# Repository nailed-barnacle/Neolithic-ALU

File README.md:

# Neolithic-ALU
This is a simple 8-bit ALU based on Ken Shirriff's dissection of the 8085's ALU at https://www.righto.com/2013/01/inside-alu-of-8085-microprocessor.html

It takes two inputs - A and B - and a number of control inputs to provide an output, one of:
- A (bypass)
- A OR B
- A AND B
- A XOR B
- A plus B with carry
- A minus B with carry 
- Complement of B
- A shifted right

Notes:

The carry input and output for arithmetic operations is inverted. To add or subtract without carry, it must be set. For other logic operations it must be set or cleared.

The zero output is inverted (i.e. set if the output is not zero).

The sign output is simply bit 7 of the result.

The bit shifted out after a right shift is the lowest input bit; it has no dedicated output. A dedicated input - shift_in - provides the high bit of the shift result.

At the time of posting, the only parts available for all components were 74HC; the circuit will operate across the 74HC range but will be faster at 5v than 3v3. I still need to measure the propagation delay but expect it to be around 60-70ns at five volts. Other equivalant parts - e.g. AHC or VLC - will probably be faster. The critical path is the chain of OR gates running right to left through the circuit.

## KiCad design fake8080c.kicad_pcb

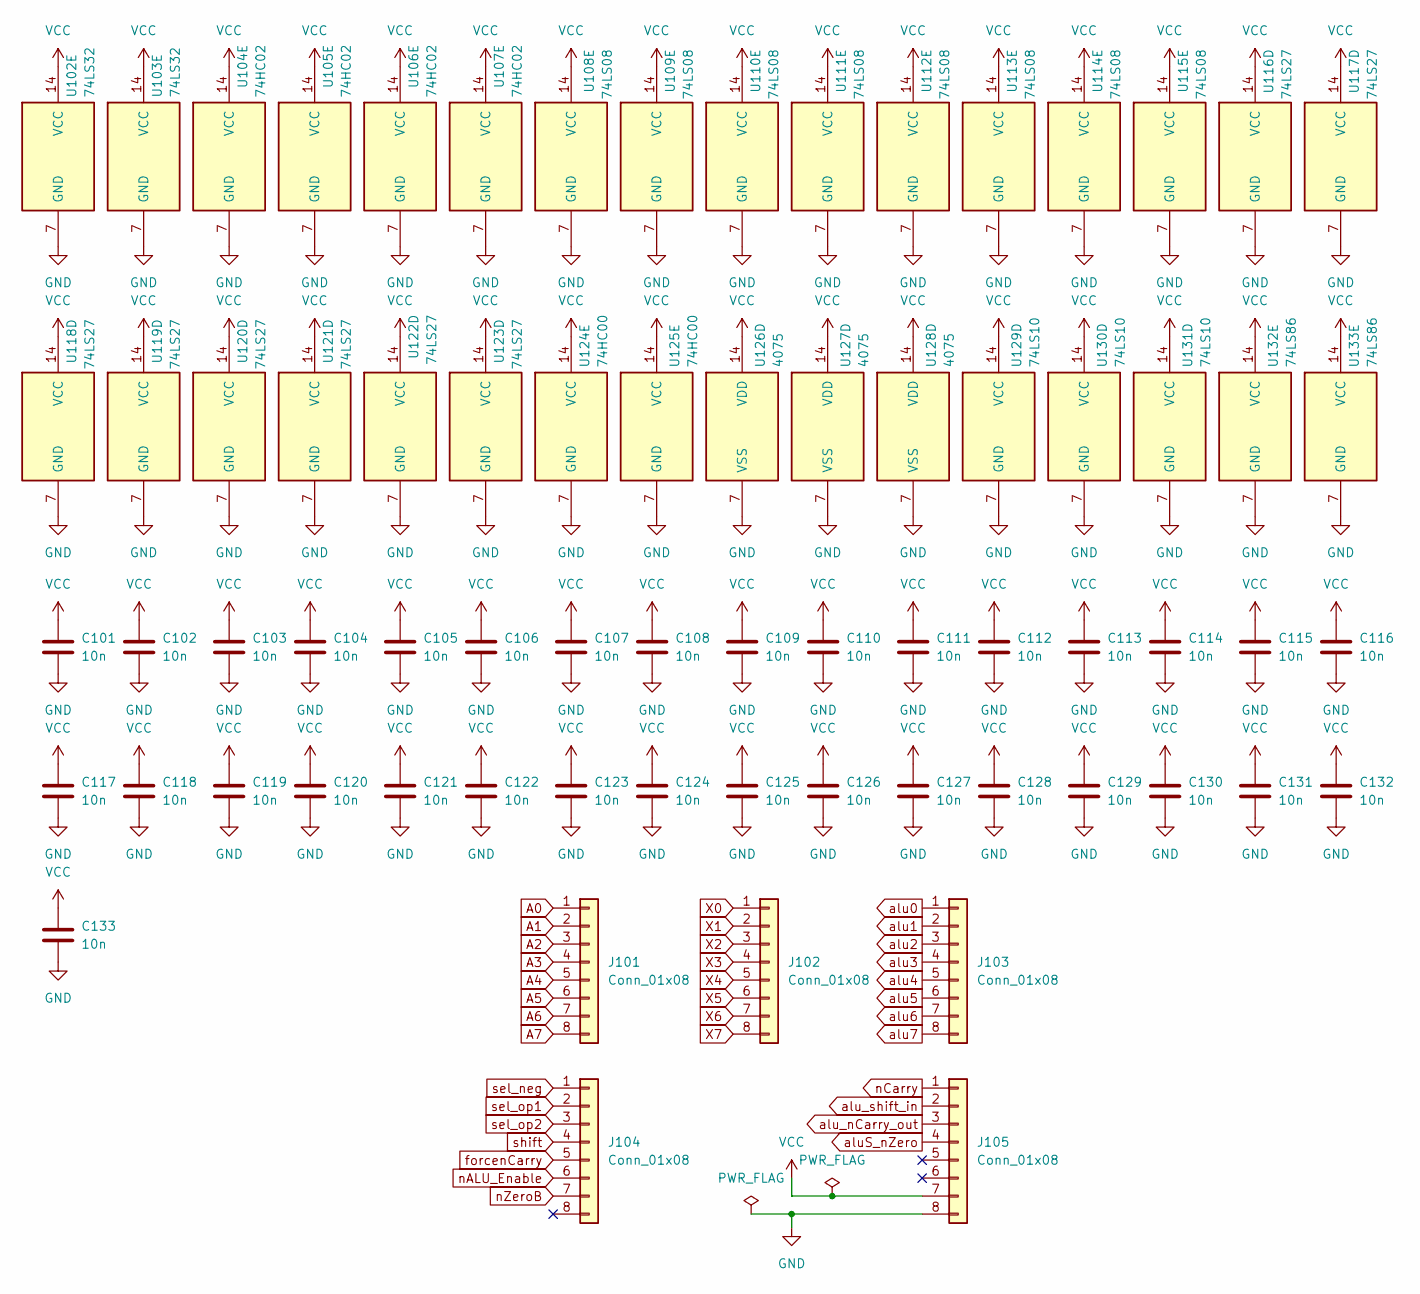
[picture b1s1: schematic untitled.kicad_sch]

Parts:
C101, C102, C103, C104, C105, C106, C107, C108, C109, C110, C111, C112, C113, C114, C115, C116, C117, C118, C119, C120, C121, C122, C123, C124, C125, C126, C127, C128, C129, C130, C131, C132, C133: 10n; C_0603_1608Metric
J101, J102, J103, J104, J105: Conn_01x08; PinHeader_1x08_P2.54mm_Vertical
U102, U103: 74LS32; SOIC-14_3.9x8.7mm_P1.27mm
U104, U105, U106, U107: 74HC02; SOIC-14_3.9x8.7mm_P1.27mm
U108, U109, U110, U111, U112, U113, U114, U115: 74LS08; SOIC-14_3.9x8.7mm_P1.27mm
U116, U117, U118, U119, U120, U121, U122, U123: 74LS27; SOIC-14_3.9x8.7mm_P1.27mm
U124, U125: 74HC00; SOIC-14_3.9x8.7mm_P1.27mm
U126, U127, U128: 4075; SOIC-14_3.9x8.7mm_P1.27mm
U129, U130, U131: 74LS10; SOIC-14_3.9x8.7mm_P1.27mm
U132, U133: 74LS86; SOIC-14_3.9x8.7mm_P1.27mm

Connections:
A0: J101.1; also elsewhere on the board
A1: J101.2; also elsewhere on the board
A2: J101.3; also elsewhere on the board
A3: J101.4; also elsewhere on the board
A4: J101.5; also elsewhere on the board
A5: J101.6; also elsewhere on the board
A6: J101.7; also elsewhere on the board
A7: J101.8; also elsewhere on the board
GND: C101.2, C102.2, C103.2, C104.2, C105.2, C106.2, C107.2, C108.2, C109.2, C110.2, C111.2, C112.2, C113.2, C114.2, C115.2, C116.2, C117.2, C118.2, C119.2, C120.2, C121.2, C122.2, C123.2, C124.2, C125.2, C126.2, C127.2, C128.2, C129.2, C130.2, C131.2, C132.2, C133.2, J105.8, U102.7 (GND), U103.7 (GND), U104.7 (GND), U105.7 (GND), U106.7 (GND), U107.7 (GND), U108.7 (GND), U109.7 (GND), U110.7 (GND), U111.7 (GND), U112.7 (GND), U113.7 (GND), U114.7 (GND), U115.7 (GND), U116.7 (GND), U117.7 (GND), U118.7 (GND), U119.7 (GND), U120.7 (GND), U121.7 (GND), U122.7 (GND), U123.7 (GND), U124.7 (GND), U125.7 (GND), U126.7 (VSS), U127.7 (VSS), U128.7 (VSS), U129.7 (GND), U130.7 (GND), U131.7 (GND), U132.7 (GND), U133.7 (GND); also elsewhere on the board
VCC: C101.1, C102.1, C103.1, C104.1, C105.1, C106.1, C107.1, C108.1, C109.1, C110.1, C111.1, C112.1, C113.1, C114.1, C115.1, C116.1, C117.1, C118.1, C119.1, C120.1, C121.1, C122.1, C123.1, C124.1, C125.1, C126.1, C127.1, C128.1, C129.1, C130.1, C131.1, C132.1, C133.1, J105.7, U102.14 (VCC), U103.14 (VCC), U104.14 (VCC), U105.14 (VCC), U106.14 (VCC), U107.14 (VCC), U108.14 (VCC), U109.14 (VCC), U110.14 (VCC), U111.14 (VCC), U112.14 (VCC), U113.14 (VCC), U114.14 (VCC), U115.14 (VCC), U116.14 (VCC), U117.14 (VCC), U118.14 (VCC), U119.14 (VCC), U120.14 (VCC), U121.14 (VCC), U122.14 (VCC), U123.14 (VCC), U124.14 (VCC), U125.14 (VCC), U126.14 (VDD), U127.14 (VDD), U128.14 (VDD), U129.14 (VCC), U130.14 (VCC), U131.14 (VCC), U132.14 (VCC), U133.14 (VCC); also elsewhere on the board
X0: J102.1; also elsewhere on the board
X1: J102.2; also elsewhere on the board
X2: J102.3; also elsewhere on the board
X3: J102.4; also elsewhere on the board
X4: J102.5; also elsewhere on the board
X5: J102.6; also elsewhere on the board
X6: J102.7; also elsewhere on the board
X7: J102.8; also elsewhere on the board
alu0: J103.1; also elsewhere on the board
alu1: J103.2; also elsewhere on the board
alu2: J103.3; also elsewhere on the board
alu3: J103.4; also elsewhere on the board
alu4: J103.5; also elsewhere on the board
alu5: J103.6; also elsewhere on the board
alu6: J103.7; also elsewhere on the board
alu7: J103.8; also elsewhere on the board
aluS_nZero: J105.4; also elsewhere on the board
alu_nCarry_out: J105.3; also elsewhere on the board
alu_shift_in: J105.2; also elsewhere on the board
forcenCarry: J104.5; also elsewhere on the board
nALU_Enable: J104.6; also elsewhere on the board
nCarry: J105.1; also elsewhere on the board
nZeroB: J104.7; also elsewhere on the board
sel_neg: J104.1; also elsewhere on the board
sel_op1: J104.2; also elsewhere on the board
sel_op2: J104.3; also elsewhere on the board
shift: J104.4; also elsewhere on the board

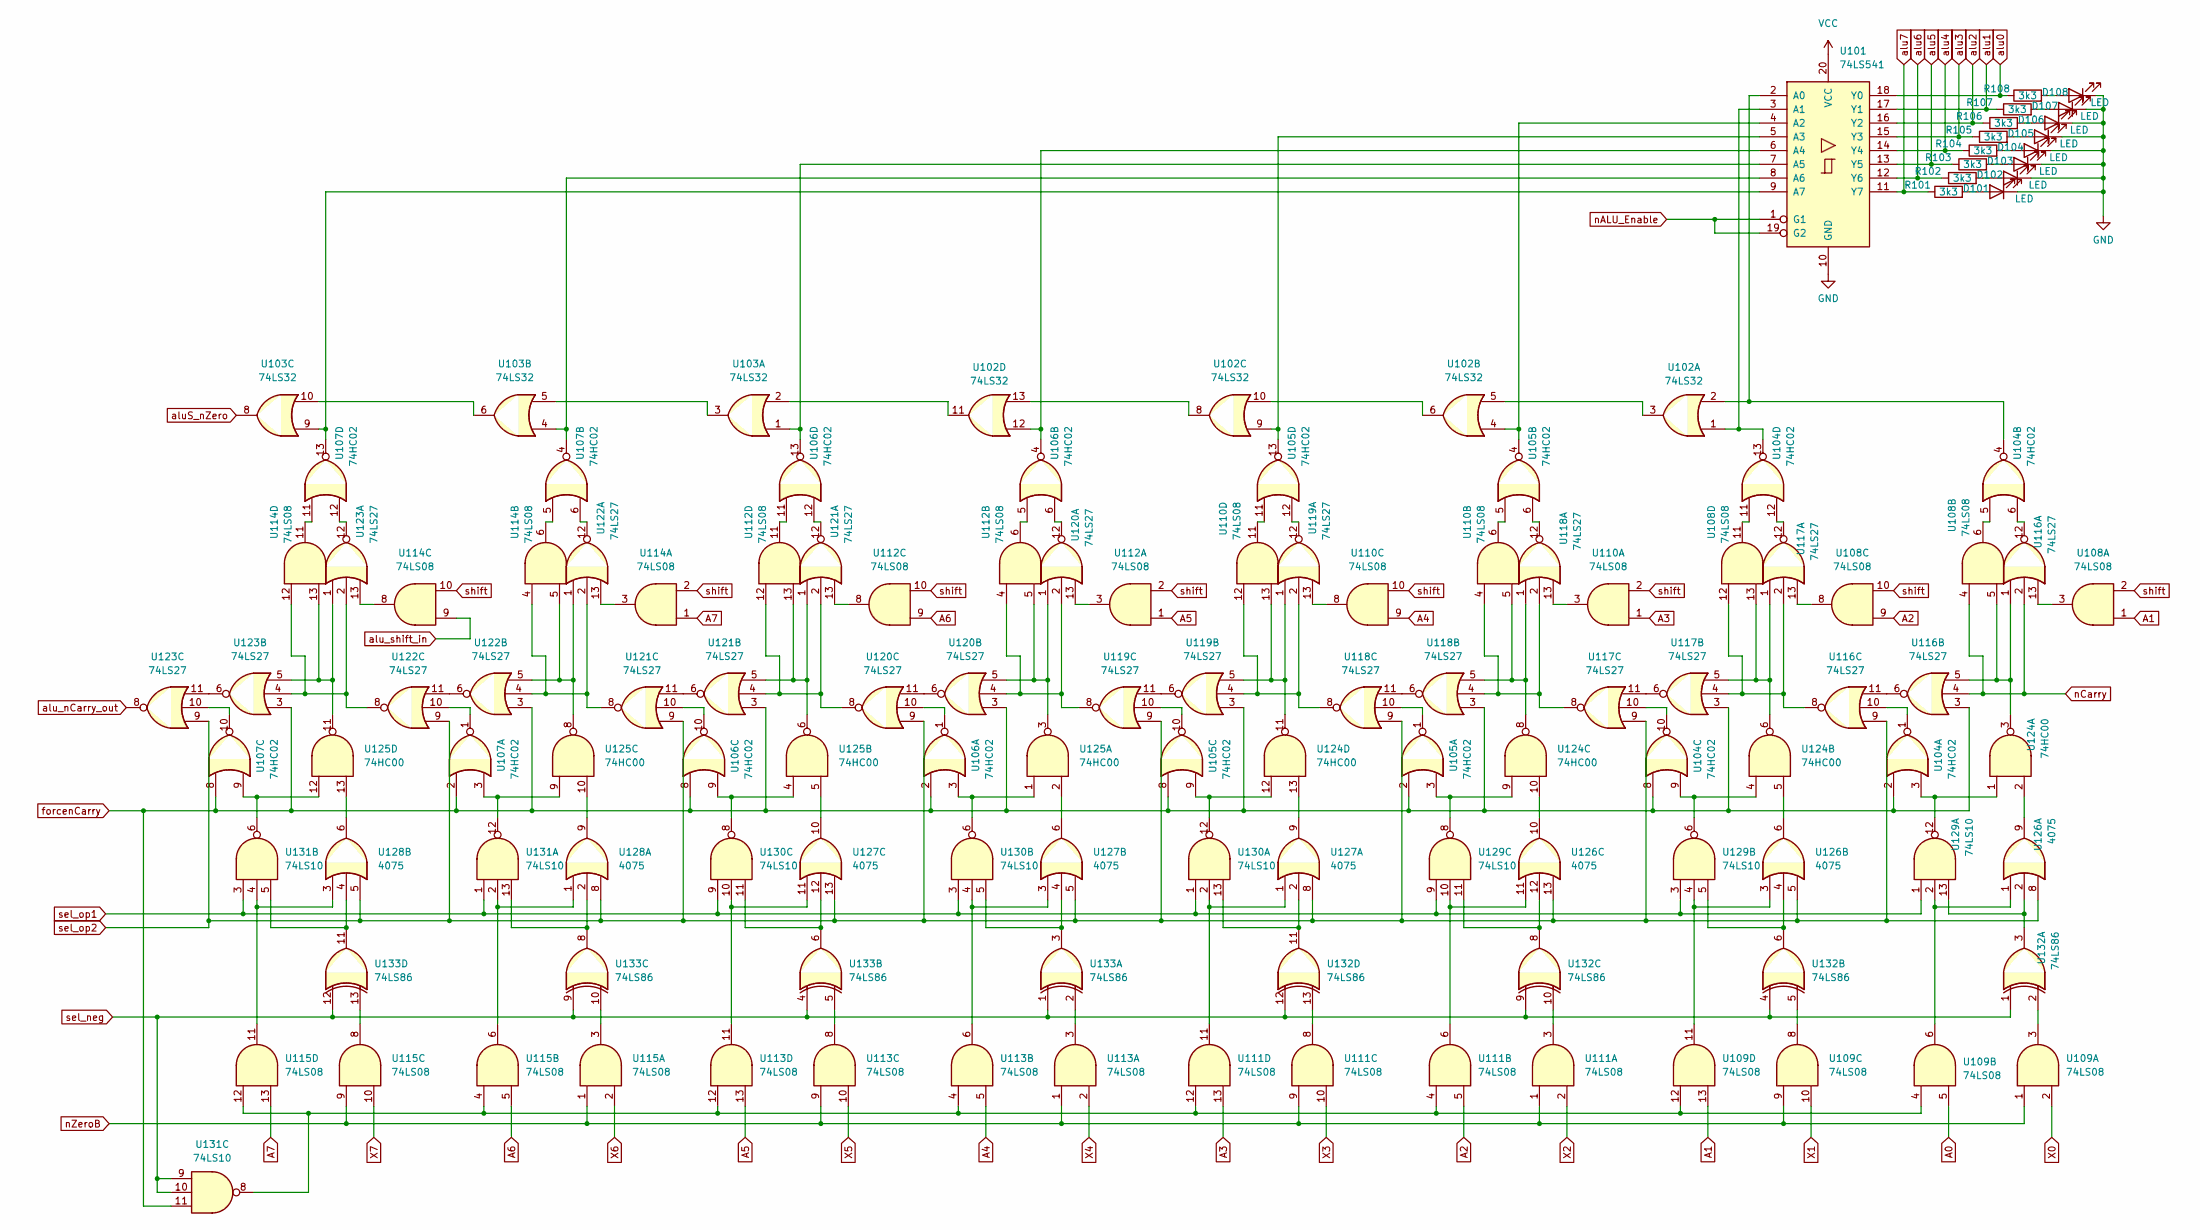
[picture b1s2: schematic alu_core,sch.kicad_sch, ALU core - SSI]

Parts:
D101, D102, D103, D104, D105, D106, D107, D108: LED; LED_0603_1608Metric_Pad1.05x0.95mm_HandSolder
R101, R102, R103, R104, R105, R106, R107, R108: 3k3; R_0603_1608Metric_Pad0.98x0.95mm_HandSolder
U101: 74LS541; SOIC-20W_7.5x12.8mm_P1.27mm
U102, U103: 74LS32; SOIC-14_3.9x8.7mm_P1.27mm
U104, U105, U106, U107: 74HC02; SOIC-14_3.9x8.7mm_P1.27mm
U108, U109, U110, U111, U112, U113, U114, U115: 74LS08; SOIC-14_3.9x8.7mm_P1.27mm
U116, U117, U118, U119, U120, U121, U122, U123: 74LS27; SOIC-14_3.9x8.7mm_P1.27mm
U124, U125: 74HC00; SOIC-14_3.9x8.7mm_P1.27mm
U126, U127, U128: 4075; SOIC-14_3.9x8.7mm_P1.27mm
U129, U130, U131: 74LS10; SOIC-14_3.9x8.7mm_P1.27mm
U132, U133: 74LS86; SOIC-14_3.9x8.7mm_P1.27mm

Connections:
A0: U109.5; also elsewhere on the board
A1: U108.1, U109.13; also elsewhere on the board
A2: U108.9, U111.5; also elsewhere on the board
A3: U110.1, U111.13; also elsewhere on the board
A4: U110.9, U113.5; also elsewhere on the board
A5: U112.1, U113.13; also elsewhere on the board
A6: U112.9, U115.5; also elsewhere on the board
A7: U114.1, U115.13; also elsewhere on the board
GND: D101.1 (K), D102.1 (K), D103.1 (K), D104.1 (K), D105.1 (K), D106.1 (K), D107.1 (K), D108.1 (K), U101.10 (GND); also elsewhere on the board
unnamed: D108.2 (A), R108.2
unnamed: D101.2 (A), R101.2
unnamed: D102.2 (A), R102.2
unnamed: D103.2 (A), R103.2
unnamed: D104.2 (A), R104.2
unnamed: D105.2 (A), R105.2
unnamed: D106.2 (A), R106.2
unnamed: D107.2 (A), R107.2
unnamed: U101.2 (A0), U102.2, U104.4
unnamed: U101.3 (A1), U102.1, U104.13
unnamed: U101.4 (A2), U102.4, U105.4
unnamed: U101.5 (A3), U102.9, U105.13
unnamed: U101.6 (A4), U102.12, U106.4
unnamed: U101.7 (A5), U103.1, U106.13
unnamed: U101.8 (A6), U103.4, U107.4
unnamed: U101.9 (A7), U103.9, U107.13
unnamed: U102.3, U102.5
unnamed: U102.6, U102.10
unnamed: U102.8, U102.13
unnamed: U102.11, U103.2
unnamed: U103.3, U103.5
unnamed: U103.6, U103.10
unnamed: U104.1, U116.10
unnamed: U104.3, U124.1, U129.12
unnamed: U104.5, U108.6
unnamed: U104.6, U116.12
unnamed: U104.9, U124.4, U129.6
unnamed: U104.10, U117.10
unnamed: U104.11, U108.11
unnamed: U104.12, U117.12
unnamed: U105.5, U110.6
unnamed: U105.6, U118.12
unnamed: U105.9, U124.12, U130.12
unnamed: U105.10, U119.10
unnamed: U105.11, U110.11
unnamed: U105.12, U119.12
unnamed: U106.1, U120.10
unnamed: U106.3, U125.1, U130.6
unnamed: U106.5, U112.6
unnamed: U106.6, U120.12
unnamed: U106.9, U125.4, U130.8
unnamed: U106.10, U121.10
unnamed: U106.11, U112.11
unnamed: U106.12, U121.12
unnamed: U107.1, U122.10
unnamed: U107.3, U125.9, U131.12
unnamed: U107.5, U114.6
unnamed: U107.6, U122.12
unnamed: U107.9, U125.12, U131.6
unnamed: U107.10, U123.10
unnamed: U107.11, U114.11
unnamed: U107.12, U123.12
unnamed: U108.3, U116.13
unnamed: U108.5, U116.1, U116.5, U124.3
unnamed: U108.8, U117.13
unnamed: U108.12, U116.8, U117.2, U117.4
unnamed: U108.13, U117.1, U117.5, U124.6
unnamed: U109.3, U132.2
unnamed: U109.4, U109.12, U111.4, U111.12, U113.4, U113.12, U115.4, U115.12, U131.8
unnamed: U109.6, U126.1, U129.2
unnamed: U109.8, U132.5
unnamed: U109.11, U126.3, U129.4
unnamed: U110.3, U118.13
unnamed: U110.4, U117.8, U118.2, U118.4
unnamed: U110.5, U118.1, U118.5, U124.8
unnamed: U110.8, U119.13
unnamed: U110.12, U118.8, U119.2, U119.4
unnamed: U110.13, U119.1, U119.5, U124.11
unnamed: U111.3, U132.10
unnamed: U111.6, U126.11, U129.10
unnamed: U111.8, U132.13
unnamed: U111.11, U127.1, U130.2
unnamed: U112.3, U120.13
unnamed: U112.4, U119.8, U120.2, U120.4
unnamed: U112.5, U120.1, U120.5, U125.3
unnamed: U112.8, U121.13
unnamed: U112.12, U120.8, U121.2, U121.4
unnamed: U112.13, U121.1, U121.5, U125.6
unnamed: U113.3, U133.2
unnamed: U113.6, U127.3, U130.4
unnamed: U113.8, U133.5
unnamed: U113.11, U127.11, U130.10
unnamed: U114.3, U122.13
unnamed: U114.4, U121.8, U122.2, U122.4
unnamed: U114.5, U122.1, U122.5, U125.8
unnamed: U114.8, U123.13
unnamed: U114.12, U122.8, U123.2, U123.4
unnamed: U114.13, U123.1, U123.5, U125.11
unnamed: U115.3, U133.10
unnamed: U115.6, U128.1, U131.2
unnamed: U115.8, U133.13
unnamed: U115.11, U128.3, U131.4
unnamed: U116.6, U116.11
unnamed: U117.6, U117.11
unnamed: U118.6, U118.11
unnamed: U105.1, U118.10
unnamed: U119.6, U119.11
unnamed: U120.6, U120.11
unnamed: U121.6, U121.11
unnamed: U122.6, U122.11
unnamed: U123.6, U123.11
unnamed: U124.2, U126.9
unnamed: U124.5, U126.6
unnamed: U105.3, U124.9, U129.8
unnamed: U124.10, U126.10
unnamed: U124.13, U127.9
unnamed: U125.2, U127.6
unnamed: U125.5, U127.10
unnamed: U125.10, U128.9
unnamed: U125.13, U128.6
unnamed: U126.2, U129.13, U132.3
unnamed: U126.4, U129.5, U132.6
unnamed: U126.12, U129.11, U132.8
unnamed: U127.2, U130.13, U132.11
unnamed: U127.12, U130.11, U133.6
unnamed: U128.4, U131.5, U133.11
unnamed: U127.4, U130.5, U133.3
unnamed: U128.2, U131.13, U133.8
VCC: U101.20 (VCC); also elsewhere on the board
X0: U109.2; also elsewhere on the board
X1: U109.10; also elsewhere on the board
X2: U111.2; also elsewhere on the board
X3: U111.10; also elsewhere on the board
X4: U113.2; also elsewhere on the board
X5: U113.10; also elsewhere on the board
X6: U115.2; also elsewhere on the board
X7: U115.10; also elsewhere on the board
alu0: R108.1, U101.18 (Y0); also elsewhere on the board
alu1: R107.1, U101.17 (Y1); also elsewhere on the board
alu2: R106.1, U101.16 (Y2); also elsewhere on the board
alu3: R105.1, U101.15 (Y3); also elsewhere on the board
alu4: R104.1, U101.14 (Y4); also elsewhere on the board
alu5: R103.1, U101.13 (Y5); also elsewhere on the board
alu6: R102.1, U101.12 (Y6); also elsewhere on the board
alu7: R101.1, U101.11 (Y7); also elsewhere on the board
aluS_nZero: U103.8; also elsewhere on the board
alu_nCarry_out: U123.8; also elsewhere on the board
alu_shift_in: U114.9; also elsewhere on the board
forcenCarry: U104.2, U104.8, U105.2, U105.8, U106.2, U106.8, U107.2, U107.8, U116.3, U117.3, U118.3, U119.3, U120.3, U121.3, U122.3, U123.3, U131.11; also elsewhere on the board
nALU_Enable: U101.1 (G1), U101.19 (G2); also elsewhere on the board
nCarry: U108.4, U116.2, U116.4; also elsewhere on the board
nZeroB: U109.1, U109.9, U111.1, U111.9, U113.1, U113.9, U115.1, U115.9; also elsewhere on the board
sel_neg: U131.9, U131.10, U132.1, U132.4, U132.9, U132.12, U133.1, U133.4, U133.9, U133.12; also elsewhere on the board
sel_op1: U129.1, U129.3, U129.9, U130.1, U130.3, U130.9, U131.1, U131.3; also elsewhere on the board
sel_op2: U116.9, U117.9, U118.9, U119.9, U120.9, U121.9, U122.9, U123.9, U126.5, U126.8, U126.13, U127.5, U127.8, U127.13, U128.5, U128.8; also elsewhere on the board
shift: U108.2, U108.10, U110.2, U110.10, U112.2, U112.10, U114.2, U114.10; also elsewhere on the board

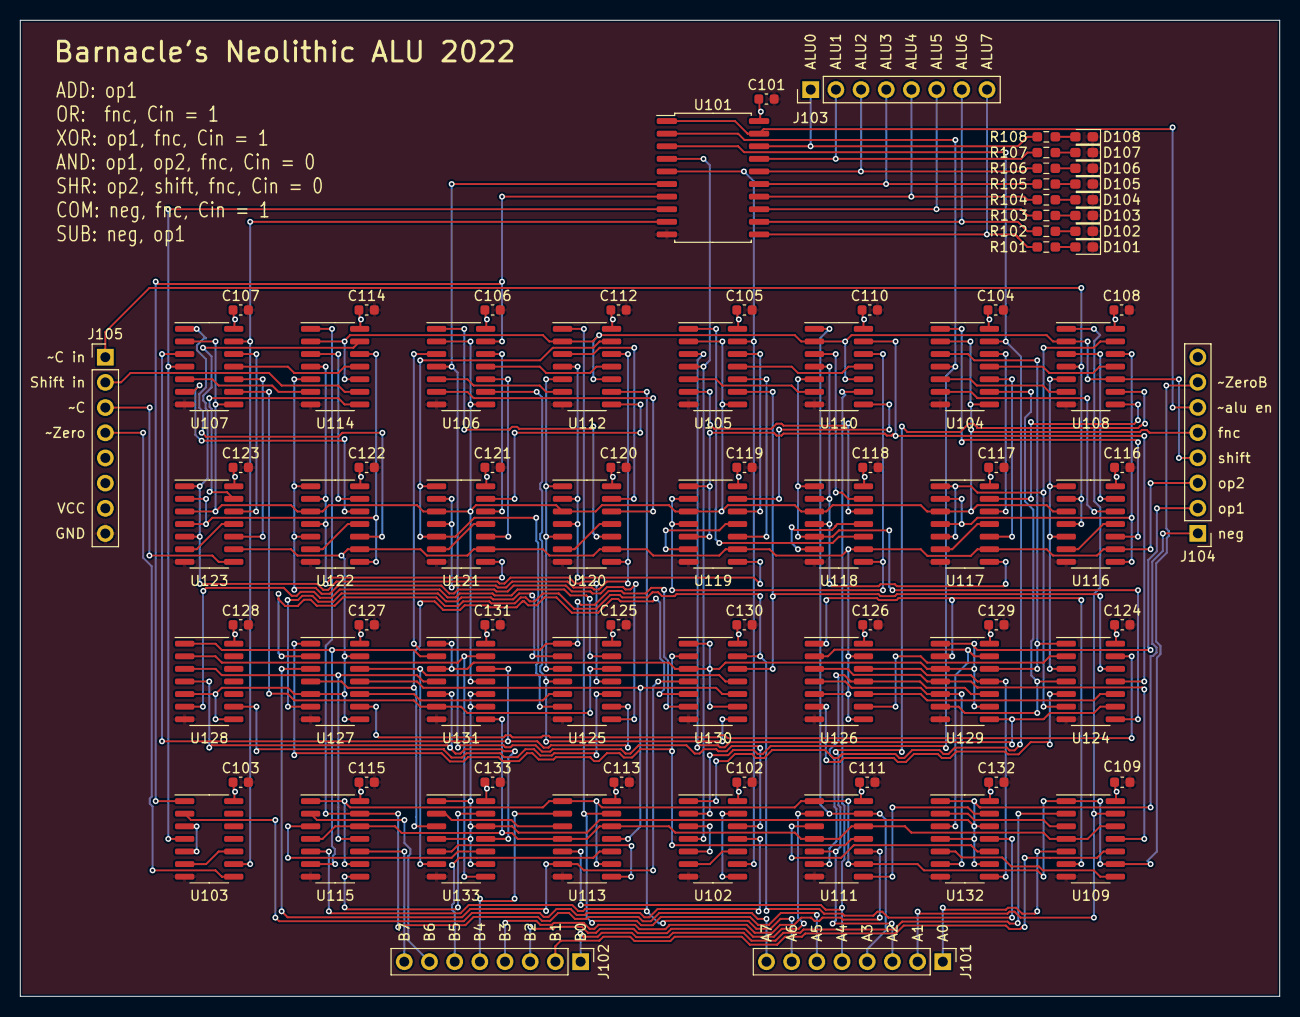
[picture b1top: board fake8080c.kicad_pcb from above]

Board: 2 copper layers, 127.0 x 98.4 mm, 87 parts (0 on the bottom side), 155 nets.

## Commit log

2022-11-09 Create LICENSE
